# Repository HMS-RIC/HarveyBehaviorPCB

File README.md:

# HarveyBehaviorPCB v2
Circuit board for Harvey Lab VR behavior rigs

## Features
This board is designed to integrate a Teensy microcontroller and a National Instruments DAQ board (NI USB-600x) with the sensors and actuators on the behavior rig. Importantly, the board is used to convey the spherical treadmill movement signals to the VR computer. The Teensy makes a digital connection to the two ball movement sensors (mounted on the base of the spherical treadmill) to make continuous reading of ball movement. It then produces three analog outputs, representing velocity in the _Yaw_, _Pitch_, and _Roll_ axes, that are read into the VR computer by the DAQ board.

Other optional features of the PCB are: 
- Driver circuit for 2 solenoid valves (e.g. for liquid rewards)
- Two lick detector circuits
- A photodiode amplifier
- Many expansion ports/connectors: BNC connections, 0.1" headers, and a serial I2C connection (Qwiic connector)

## Fabrication
The full fabrication design is included in the [Gerber Zip File](PCB_v2_KiCAD/Gerbers/HarveyBehaviorPCB_v2.zip?raw=true). You can upload this file to any PCB fabricator to get a quote and place an order. (The board does not have any special features, so the default settings for PCB manufacture are probably fine.) One a relatively low-cost option for a board this size is the $33/board (3 board minimum) special at [Advanced Circuits](https://www.advancedpcb.com/en-us/33-each-special/).

## Assembly
The [Bill of Materials](HarveyBehaviorPCB_v2_BOM.xlsx?raw=true) (BOM) file has the full list of components. Everything but the optional I2C connector is a through-hole part and can be soldered on with a simple soldering iron (and [proper technique](https://mightyohm.com/files/soldercomic/FullSolderComic_EN.pdf)). The board is divided up into labeled regions that describe their high-level function and allow you to populate only the subset of components that you plan to use:
- **Ball sensor connectors**: The board is designed to work with two types of ball sensor ([ADNS-9800](https://www.tindie.com/products/citizenjoe/adns-9800-motion-sensor/) and [PMW3360](https://www.tindie.com/products/citizenjoe/pmw3360-motion-sensor/)). Chose one and populate the appropriate connector. (Also be sure to use the correct Teensy firmware for your ball sensor.)
- **Valve driver circuit**, **Lick and photodiode circuits**: These are optional functionalities. Only populate these regions if you plan to use them.
- **LP filters for velocity signals**: These are not optional. They low-pass filter the Teensy's digital (PWM) output to form a smooth analog signal for the NI board to acquire.
- **User 3/4 voltage-limiting circuit**: This is necessary if you plan to use the NI board's analog output pins (_AO-0_, _AO-1_) to control the voltage on _User-3_ and _User-4_. This circuit protects the Teensy from an accidental +5V output from the NI board (since the Teensy 4.0 cannot handle >3.3V inputs).
- **Jumpers JP2, JP3**: Optional. Short these jumpers (i.e., connect the pins within each jumper) to enable the NI analog output (_AO-0/1_, a.k.a. _User-3/4_) to control the valves.
- **Jumpers JP4, JP5**: Optional. In their default state they enable the I2C connector and disable the _MOT1_/_MOT2_ connections to the ball sensors. The _MOTx_ lines are not used during typical operation, so these jumpers are unlikely to be used.

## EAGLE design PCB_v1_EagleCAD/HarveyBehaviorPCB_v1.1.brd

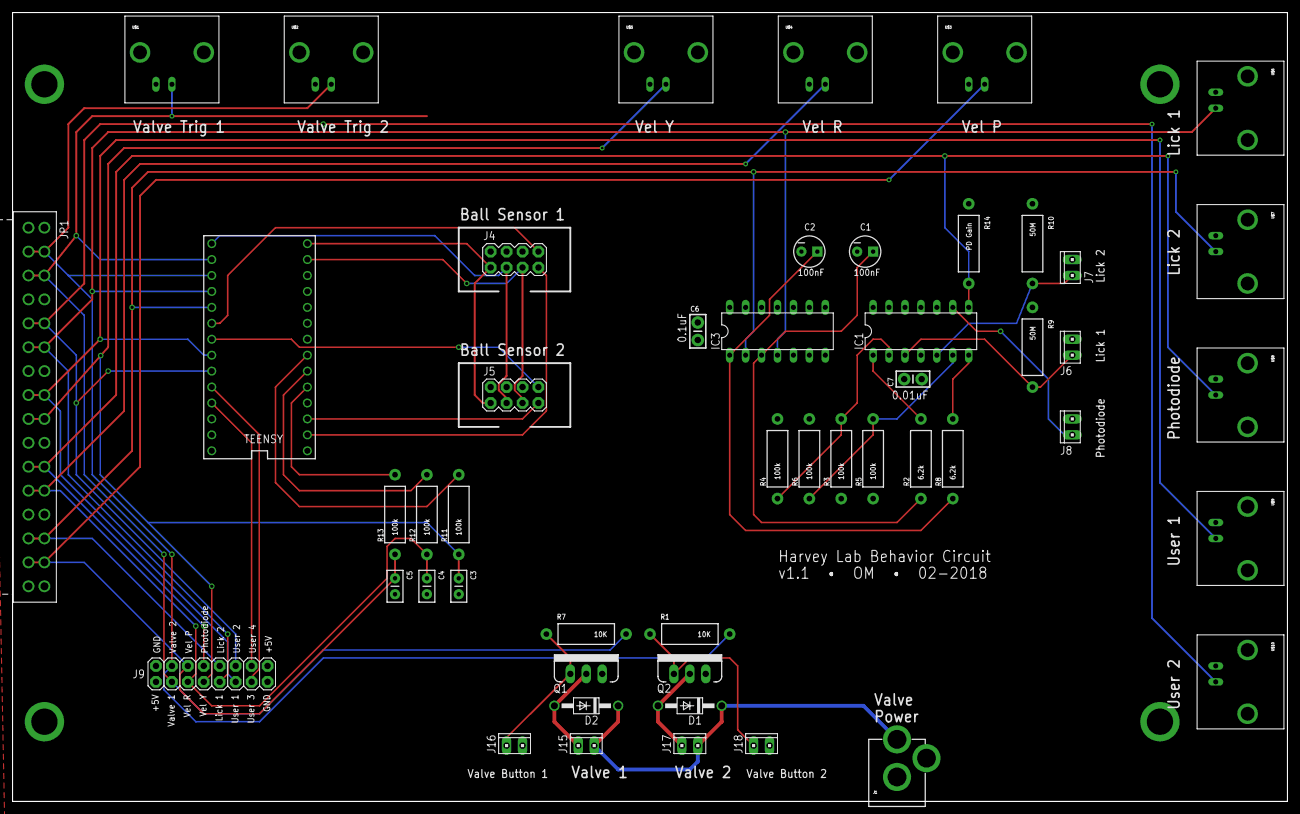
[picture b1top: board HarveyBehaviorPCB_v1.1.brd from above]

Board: 2 copper layers, 203.2 x 125.7 mm, 54 parts (0 on the bottom side), 38 nets.

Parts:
C1, C2: 100nF; CPOL-RADIAL-10UF-25V
C3, C4, C5: 0.22uF; CAP-PTH-SMALL2
C6: 0.1uF; CAP-PTH-SMALL-KIT
C7: 0.01uF; CAP-PTH-SMALL-KIT
D1, D2: 1N4148; DO41-10
IC1: LT1490A; DIL14
IC3: 40106N; DIL14
J1: POWER_JACKPTH; POWER_JACK_PTH
J2, J3, J10, J11: SMTSO-256-ET-0.165DIA
J4: BALL_1; 2X4
J5: BALL_2; 2X4
J6, J7: 10X02MTA
J8: Photodiode; 10X02MTA
J9: 2X8
J15: Valve 1; 10X02MTA
J16: Valve 1 Switch; 10X02MTA
J17: Valve 2; 10X02MTA
J18: Valve 2 Switch; 10X02MTA
JP1: M16; 1X16_TERM_BLOCK_0.15"
Q1, Q2: MOSFET-NCHANNELFQP30N06L; TO220V
R1, R7: 10K; AXIAL-0.5
R2, R8: 6.2k; AXIAL-0.5
R3, R4, R5, R6, R11, R12, R13: 100k; AXIAL-0.5
R9, R10: 50M; AXIAL-0.5
R14: PD Gain; AXIAL-0.5
TEENSY: TEENSY_3.1-3.2_DIL; TEENSY_3.0-3.2&LC_DIL
U$1, U$2, U$3, U$4, U$5, U$6, U$7, U$8, U$9, U$10: BNCPTH; BNC

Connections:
5V: C6.1, C7.1, IC1.4, IC3.14, J4.2, J5.2, J9.1, J9.16, J16.1, J18.1, R3.P$1, R5.P$1, R9.P$1, R10.P$1, TEENSY.VIN
CS1: J4.7, TEENSY.0
CS2: J5.7, TEENSY.1
GND: C1.2, C2.2, C3.2, C4.2, C5.2, C6.2, C7.2, IC1.10, IC1.11, IC1.12, IC1.13, IC3.5, IC3.7, IC3.9, IC3.11, IC3.13, J1.GND, J1.GNDBREAK, J2.P$1, J3.P$1, J4.4, J4.6, J5.4, J5.6, J6.1, J7.1, J8.1, J9.2, J9.15, J10.P$1, J11.P$1, JP1.1, JP1.4, JP1.7, JP1.10, JP1.13, JP1.16, JP1.17, JP1.20, JP1.23, JP1.26, JP1.29, JP1.32, Q1.3, Q2.3, R4.P$2, R6.P$2, TEENSY.AGND, TEENSY.GND, U$1.GND, U$2.GND, U$3.GND, U$4.GND, U$5.GND, U$6.GND, U$7.GND, U$8.GND, U$9.GND, U$10.GND
LICK_1: IC3.4, J9.9, JP1.6, JP1.22, TEENSY.16/A2, U$6.S
LICK_1_IN: IC1.3, J6.2, R9.P$2
LICK_2: IC3.2, J9.10, JP1.14, JP1.30, TEENSY.17/A3, U$7.S
LICK_2_IN: IC1.5, J7.2, R10.P$2
MISO: J4.1, J5.1, TEENSY.12
MOSI: J4.5, J5.5, TEENSY.11
MOT1: J4.8, TEENSY.18/A4
MOT2: J5.8, TEENSY.19/A5
unnamed: C1.1, IC3.3, R2.P$1
unnamed: IC1.1, R2.P$2
unnamed: IC1.2, R3.P$2, R4.P$1
unnamed: D2.A, J15.2, Q1.2
unnamed: J16.2, Q1.1, R7.P$2
unnamed: D1.A, J17.2, Q2.2
unnamed: J18.2, Q2.1, R1.P$2
unnamed: IC1.6, R5.P$2, R6.P$1
unnamed: C2.1, IC3.1, R8.P$1
unnamed: IC1.7, R8.P$2
PHOTODIODE: IC1.8, J9.8, JP1.11, JP1.27, R14.P$2, U$8.S
PHOTODIODE_IN: IC1.9, J8.2
SCK: J4.3, J5.3, TEENSY.13
USER_1: J9.11, JP1.8, JP1.24, TEENSY.20/A6, U$9.S
USER_2: J9.12, JP1.5, JP1.21, TEENSY.21/A7, U$10.S
USER_3: J9.13, TEENSY.22/A8
USER_4: J9.14, TEENSY.23/A9
VALVE_1_TRIG: J9.3, JP1.3, JP1.19, R7.P$1, TEENSY.14/A0, U$1.S
VALVE_2_TRIG: J9.4, JP1.2, JP1.18, R1.P$1, TEENSY.15/A1, U$2.S
VEL_P: C5.1, J9.6, JP1.15, JP1.31, R13.P$1, U$3.S
VEL_P_PWM: R13.P$2, TEENSY.3
VEL_R: C4.1, J9.5, JP1.12, JP1.28, R12.P$1, U$4.S
VEL_R_PWM: R12.P$2, TEENSY.4
VEL_Y: C3.1, J9.7, JP1.9, JP1.25, R11.P$1, U$5.S
VEL_Y_PWM: R11.P$2, TEENSY.5
VSOL: D1.C, D2.C, J1.PWR, J15.1, J17.1

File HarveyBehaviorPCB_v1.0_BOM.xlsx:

Part | Value | Device | Package | Description
C1 | 100nF
C2 | 100nF
C3 | 0.22uF
C4 | 0.22uF
C5 | 0.22uF
C6 | 0.1uF
C7 | 0.01uF
D1 | 1N4148 | 1N4004 |  | DIODE
D2 | 1N4148 | 1N4004 |  | DIODE
IC1 | LT1490A |  |  | Quad Wideband, Low Power Current Feedback OP AMP
IC3 | 40106N |  |  | Hex SCHMITT TRIGGER
J1 |  |  |  | Power Jack
J2 |  | M01SMTSO-256-ET-0.165DIA | SMTSO-256-ET-0.165DIA | Header 1
J3 |  | M01SMTSO-256-ET-0.165DIA | SMTSO-256-ET-0.165DIA | Header 1
J4 | BALL_1 | M04X2 | 2X4 | .1 header | two rows of four."
J5 | BALL_2 | M04X2 | 2X4 | .1 header | two rows of four."
J6 |  | MTA02-100 | 10X02MTA | AMP connector
J7 |  | MTA02-100 | 10X02MTA | AMP connector
J8 | Photodiode | MTA02-100 | 10X02MTA | AMP connector
J9 |  | M08X2 | 2X8 | .1 headers | two rows of 8 each"
J10 |  | M01SMTSO-256-ET-0.165DIA | SMTSO-256-ET-0.165DIA | Header 1
J11 |  | M01SMTSO-256-ET-0.165DIA | SMTSO-256-ET-0.165DIA | Header 1
J15 | Valve 1 | MTA02-100 | 10X02MTA | AMP connector
J16 | Valve 1 Switch | MTA02-100 | 10X02MTA | AMP connector
J17 | Valve 2 | MTA02-100 | 10X02MTA | AMP connector
J18 | Valve 2 Switch | MTA02-100 | 10X02MTA | AMP connector
JP1 | M16 | M16 | 1X16_TERM_BLOCK_0.15",1x16 .1" header"
Q1 | MOSFET-NCHANNELFQP30N06L |  | TO220V | Common NMOSFET Parts
Q2 | MOSFET-NCHANNELFQP30N06L |  | TO220V | Common NMOSFET Parts
R1 | 10K |  |  | Resistor
R2 | 6.2k |  |  | Resistor
R3 | 100k |  |  | Resistor
R4 | 100k |  |  | Resistor
R5 | 100k |  |  | Resistor
R6 | 100k |  |  | Resistor
R7 | 10K |  |  | Resistor
R8 | 6.2k |  |  | Resistor
R9 | 50M |  |  | Resistor
R10 | 50M |  |  | Resistor
R11 | 100k |  |  | Resistor
R12 | 100k |  |  | Resistor
R13 | 100k |  |  | Resistor
R14 | PD Gain |  |  | Resistor
TEENSY | TEENSY_3.1-3.2_DIL | TEENSY_3.1-3.2_DIL | TEENSY_3.0-3.2&LC_DIL | Teensy 3.1 or 3.2 in a DIL Layout.
U$1 | BNCPTH | BNCPTH | BNC | BNC Connector, Mouser Part# 5227161
U$2 | BNCPTH | BNCPTH | BNC | BNC Connector, Mouser Part# 5227161
U$3 | BNCPTH | BNCPTH | BNC | BNC Connector, Mouser Part# 5227161
U$4 | BNCPTH | BNCPTH | BNC | BNC Connector, Mouser Part# 5227161
U$5 | BNCPTH | BNCPTH | BNC | BNC Connector, Mouser Part# 5227161
U$6 | BNCPTH | BNCPTH | BNC | BNC Connector, Mouser Part# 5227161
U$7 | BNCPTH | BNCPTH | BNC | BNC Connector, Mouser Part# 5227161
U$8 | BNCPTH | BNCPTH | BNC | BNC Connector, Mouser Part# 5227161
U$9 | BNCPTH | BNCPTH | BNC | BNC Connector, Mouser Part# 5227161
U$10 | BNCPTH | BNCPTH | BNC | BNC Connector, Mouser Part# 5227161

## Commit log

2018-10-03 initial commit (v1.2)
2018-10-03 Rename some files
2018-10-03 Create LICENSE
2018-10-03 Add PDF of schematic for v1.2
2024-10-01 Convert to KiCad and update design to v2.0
2024-10-07 Make Gerbers for v2.0
2024-11-08 Update .gitignore; Add datasheet for ball sensor cable
2024-11-08 Remove backup files
2024-11-08 Rearrange files
2024-11-27 Update PCB render
2024-12-02 [PCB] Increase width of copper pads on a few footprints; v2.0 -> v2.01
2024-12-05 Update BOM
2024-12-05 Update HarveyBehaviorPCB_v2_BOM.xlsx
    Added the Digikey part # for the capacitors
2025-01-03 Fix spelling errors

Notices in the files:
parts and their libraries:
SparkFun-Connectors: Licensing: Creative Commons ShareAlike 4.0 International - https://creativecommons.org/licenses/by-sa/4.0
